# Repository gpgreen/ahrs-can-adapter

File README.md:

# ahrs-can-adapter

KiCad design for a CAN adapter to a Dronecad flight board. The MCU is a
stm32f107rbt6.

## Changes

- Rev A
  Original

## Firmware

[Firmware](https://github.com/gpgreen/ahrs-can-adapter)

## Connections to Segger JTAG

I have put test points on the board, so that pogo pins can be used to program
the MCU.

[jlink web page](https://www.segger.com/products/debug-probes/j-link/technology/interface-description/)
```
**** 20 Pin connector for JTAG
                -------
    VTref      1|*   *|2 NC
    nTRST      3|*   *|4 GND
    TDI        5|*   *|6 GND
    TMS        7|*   *|8 GND
    TCK        9|*   *|10 GND
    RTCK      11|*   *|12 GND
    TDO       13|*   *|14 GND
    RESET     15|*   *|16 GND*
    DBGRQ     17|*   *|18 GND*
    5V Supply 19|*   *|20 GND*
                -------
```
From a 20pin JTAG connector, run wires to the following test pads to connect a debugger:
```
VTRef 1  <-> 3V3
SWDIO 7  <-> SWD
SWCLK 9  <-> SWC
RESET 15 <-> RST
GND   4  <-> GND
```

## Running SEGGER JLink

Run the JLink GDB server via the following:
```
JLinkGDBServer -if SWD -device STM32F103CB
```

GDB can be connected via the following:
```
gdb-multiarch --command=jlink-stm32.gdb target/thumbv7m/debug/main
```

## Running ocd
```
openocd -f interface/stlink-v3.cfg -f target/stm32f1x.cfg
```

## Credits

as always, thanks for the good work
- [Adafruit](https://www.adafruit.com)

## License

Licensed under

- MIT license ([LICENSE-MIT](LICENSE-MIT) or http://opensource.org/licenses/MIT)

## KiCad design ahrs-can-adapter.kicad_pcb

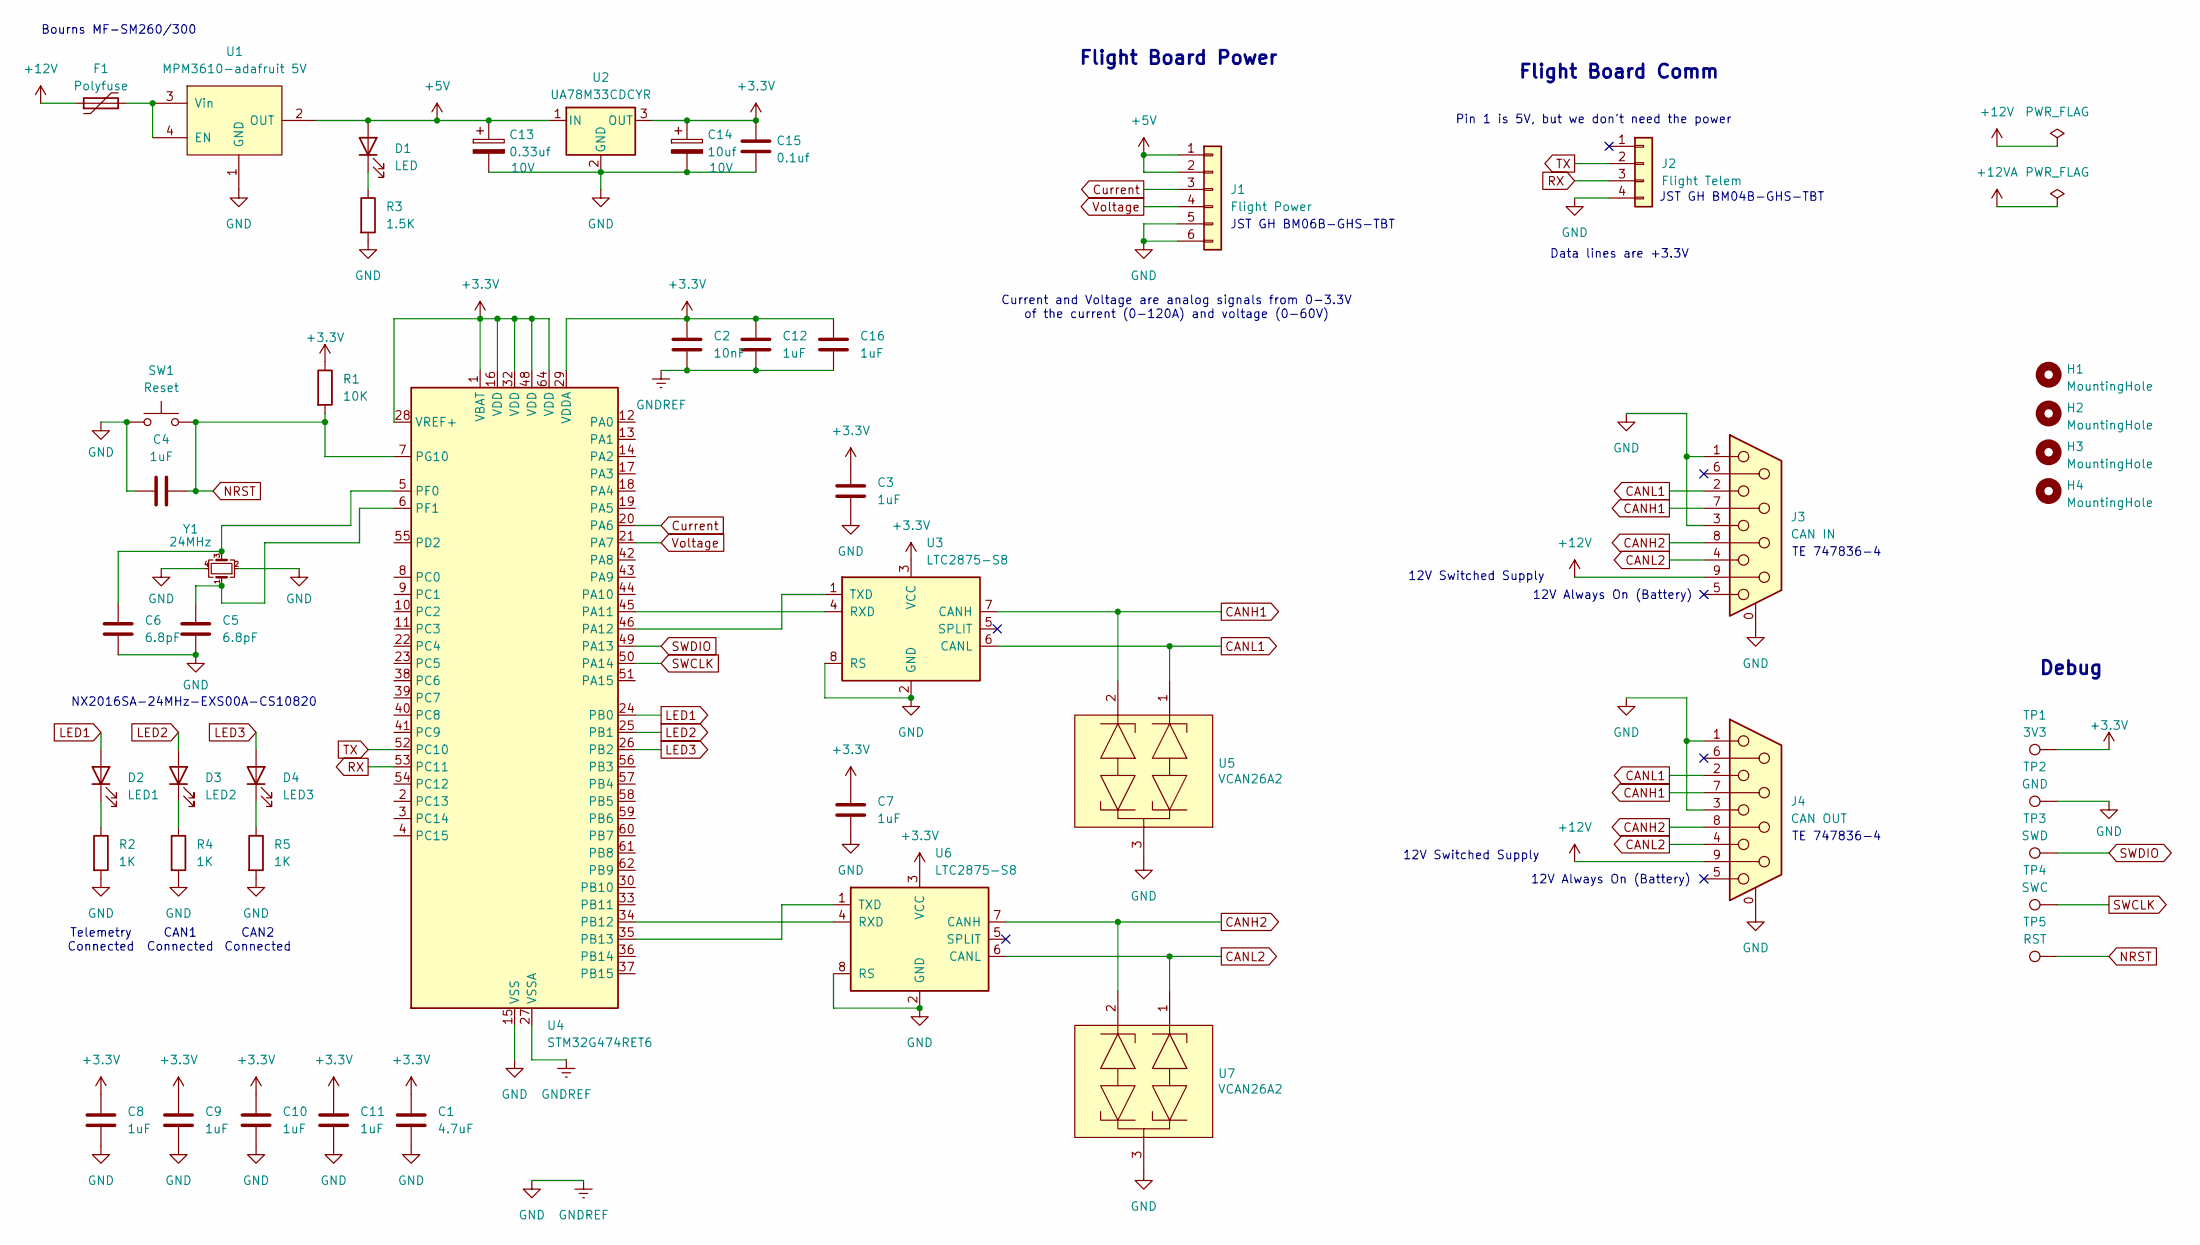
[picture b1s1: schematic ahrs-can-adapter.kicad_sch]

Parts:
C1: 4.7uF; C_0603_1608Metric
C2: 10nF; C_0603_1608Metric
C3, C4, C7, C8, C9, C10, C11, C12, C16: 1uF; C_0603_1608Metric
C5, C6: 6.8pF; C_0603_1608Metric
C13: 0.33uf; CP_EIA-3216-18_Kemet-A_HandSolder; Voltage 10V
C14: 10uf; CP_EIA-3216-18_Kemet-A_HandSolder; Voltage 10V
C15: 0.1uf; C_0603_1608Metric
D1: LED; LED_0805_2012Metric
D2: LED1; LED_0805_2012Metric
D3: LED2; LED_0805_2012Metric
D4: LED3; LED_0805_2012Metric
F1: Polyfuse; Fuse_Bourns_MF-SM_7.98x5.44mm
H1, H2, H3, H4: MountingHole; MountingHole_2.5mm_Pad
J1: Flight Power; JST_GH_BM06B-GHS-TBT_1x06-1MP_P1.25mm_Vertical
J2: Flight Telem; JST_GH_BM04B-GHS-TBT_1x04-1MP_P1.25mm_Vertical
J3: CAN IN; DSUB-9_Socket_Horizontal_P2.77x2.84mm_EdgePinOffset14.56mm_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
J4: CAN OUT; DSUB-9_Socket_Horizontal_P2.77x2.84mm_EdgePinOffset14.56mm_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
R1: 10K; R_0603_1608Metric
R2, R4, R5: 1K; R_0603_1608Metric
R3: 1.5K; R_0603_1608Metric
SW1: Reset; OnShine KPT-1187B
TP1: 3V3; TestPoint_Pad_D2.0mm
TP2: GND; TestPoint_Pad_D2.0mm
TP3: SWD; TestPoint_Pad_D2.0mm
TP4: SWC; TestPoint_Pad_D2.0mm
TP5: RST; TestPoint_Pad_D2.0mm
U1: MPM3610-adafruit 5V; Adafruit_MPM3610
U2: UA78M33CDCYR; SOT-223-3_TabPin2
U3, U6: LTC2875-S8; SOIC-8_3.9x4.9mm_P1.27mm
U4: STM32G474RET6; LQFP-64_10x10mm_P0.5mm
U5, U7: VCAN26A2; SOT-323_SC-70
Y1: 24MHz; Crystal_SMD_2016-4Pin_2.0x1.6mm

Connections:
+3.3V: C1.1, C2.1, C3.1, C7.1, C8.1, C9.1, C10.1, C11.1, C12.1, C14.1, C15.1, C16.1, R1.1, TP1.1 (1_1), U2.3 (OUT), U3.3 (VCC), U4.1 (VBAT), U4.16 (VDD), U4.28 (VREF+), U4.29 (VDDA), U4.32 (VDD), U4.48 (VDD), U4.64 (VDD), U6.3 (VCC)
+5V: C13.1, D1.2 (A), J1.1, J1.2, U1.2 (OUT), U2.1 (IN)
+12V: F1.1, J3.9 (9_9), J4.9 (9_9)
CANH1: J3.7 (7_7), J4.7 (7_7), U3.7 (CANH), U5.2
CANH2: J3.8 (8_8), J4.8 (8_8), U6.7 (CANH), U7.2
CANL1: J3.2 (2_2), J4.2 (2_2), U3.6 (CANL), U5.1
CANL2: J3.4 (4_4), J4.4 (4_4), U6.6 (CANL), U7.1
Current: J1.3, U4.20 (PA6)
GND: C1.2, C2.2, C3.2, C4.2, C5.2, C6.2, C7.2, C8.2, C9.2, C10.2, C11.2, C12.2, C13.2, C14.2, C15.2, C16.2, J1.5, J1.6, J2.4, J3.0 (PAD), J3.1 (1_1), J3.3 (3_3), J3.SH (PAD_0), J4.0 (PAD), J4.1 (1_1), J4.3 (3_3), J4.SH (PAD_0), R2.2, R3.2, R4.2, R5.2, SW1.1, TP2.1 (1_1), U1.1 (GND), U2.2 (GND), U3.2 (GND), U3.8 (RS), U4.15 (VSS), U4.27 (VSSA), U4.31 (VSS), U4.47 (VSS), U4.63 (VSS), U5.3, U6.2 (GND), U6.8 (RS), U7.3, Y1.2, Y1.4
LED1: D2.2 (A), U4.24 (PB0)
LED2: D3.2 (A), U4.25 (PB1)
LED3: D4.2 (A), U4.26 (PB2)
NRST: C4.1, R1.2, SW1.2, TP5.1 (1_1), U4.7 (PG10)
unnamed: D1.1 (K), R3.1
unnamed: D2.1 (K), R2.1
unnamed: D3.1 (K), R4.1
unnamed: D4.1 (K), R5.1
unnamed: F1.2, U1.3 (Vin), U1.4 (EN)
unnamed: U3.4 (RXD), U4.45 (PA11)
unnamed: U3.1 (TXD), U4.46 (PA12)
unnamed: U4.34 (PB12), U6.4 (RXD)
unnamed: U4.35 (PB13), U6.1 (TXD)
unnamed: C6.1, U4.5 (PF0), Y1.3
unnamed: C5.1, U4.6 (PF1), Y1.1
RX: J2.3, U4.53 (PC11)
SWCLK: TP4.1 (1_1), U4.50 (PA14)
SWDIO: TP3.1 (1_1), U4.49 (PA13)
TX: J2.2, U4.52 (PC10)
Voltage: J1.4, U4.21 (PA7)

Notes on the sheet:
Telemetry Connected
TE 747836-4
CAN2 Connected
CAN1 Connected
Debug
JST GH BM04B-GHS-TBT
12V Switched Supply
12V Always On (Battery)
Pin 1 is 5V, but we don't need the power
JST GH BM06B-GHS-TBT
Flight Board Power
NX2016SA-24MHz-EXS00A-CS10820
Current and Voltage are analog signals from 0-3.3V of the current (0-120A) and voltage (0-60V)
Flight Board Comm
Bourns MF-SM260/300
Data lines are +3.3V

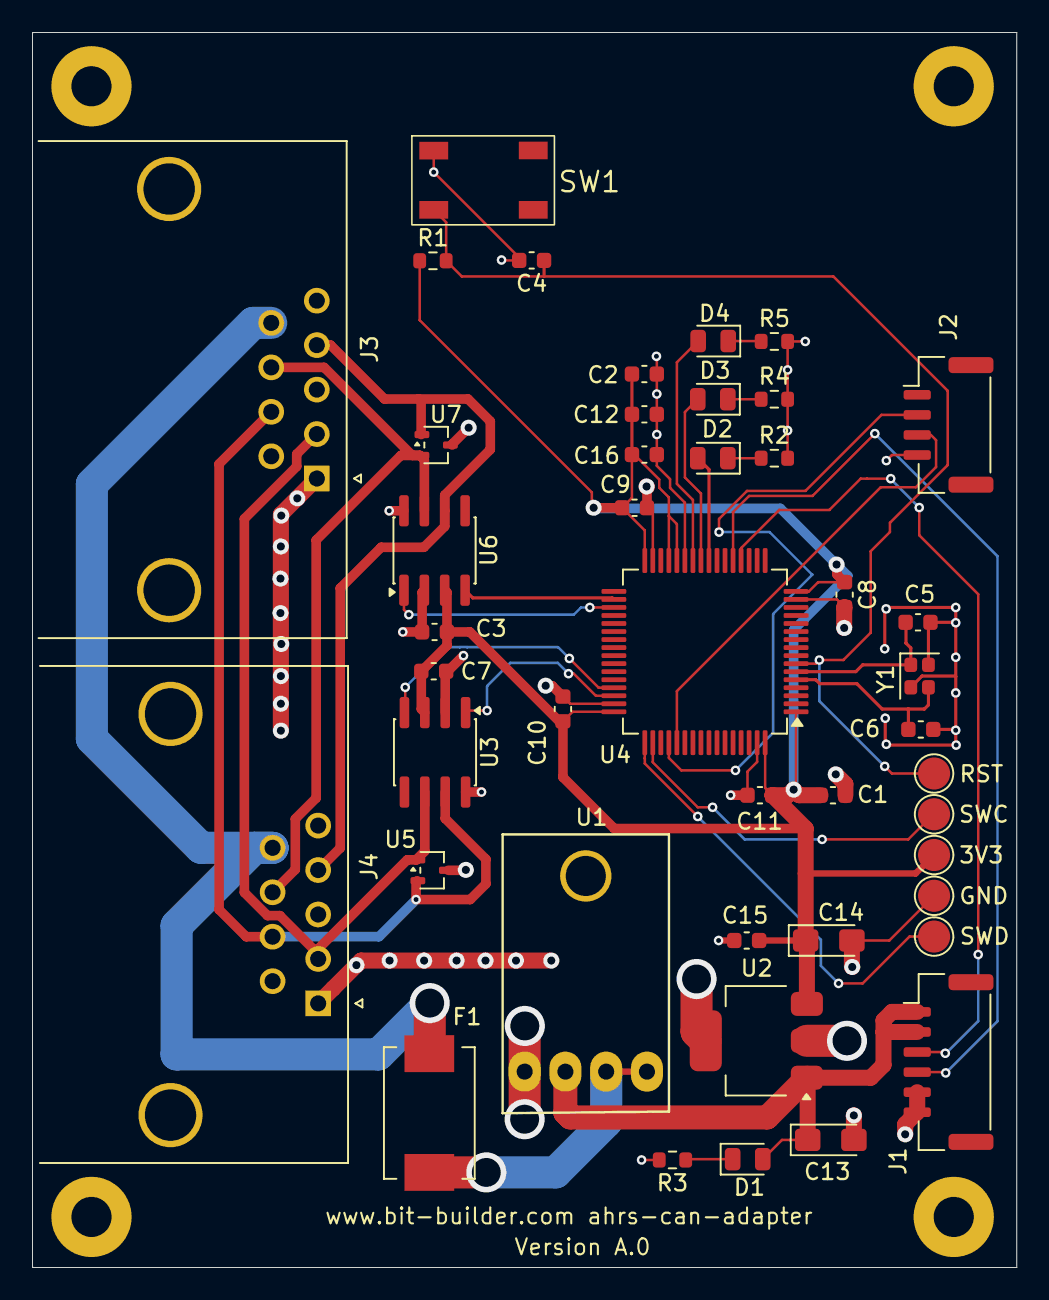
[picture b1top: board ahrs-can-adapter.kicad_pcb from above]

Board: 2 copper layers, 61.3 x 77.0 mm, 48 parts (0 on the bottom side), 29 nets.

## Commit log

2026-03-04 Fixed crystal circuit
2026-03-17 Changed flight board connectors
2026-03-24 Changed MCU to stm32g474ret6
2026-03-26 updated crystal circuit
2026-03-27 update crystal footprint
2026-04-12 Changed telemetry uart pins
